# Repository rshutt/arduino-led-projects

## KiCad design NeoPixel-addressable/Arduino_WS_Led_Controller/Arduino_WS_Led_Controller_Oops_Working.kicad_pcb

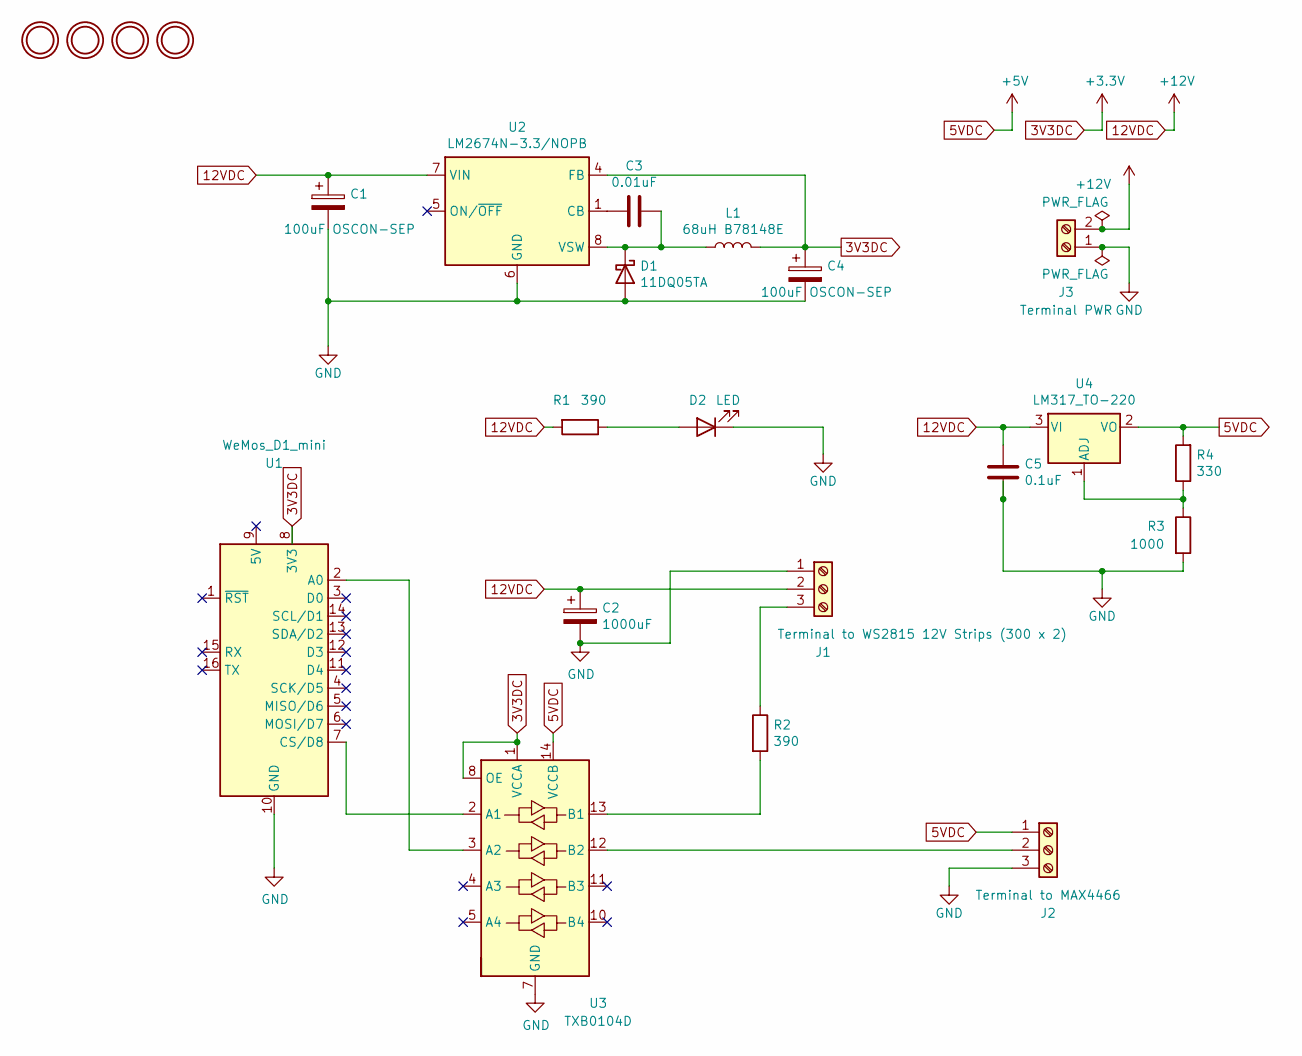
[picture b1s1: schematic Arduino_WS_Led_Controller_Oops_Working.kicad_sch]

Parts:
C1, C4: 100uF OSCON-SEP; CP_Radial_D8.0mm_P3.50mm
C2: 1000uF; CP_Radial_D10.0mm_P2.50mm
C3: 0.01uF; C_Disc_D5.0mm_W2.5mm_P5.00mm
C5: 0.1uF; C_Disc_D5.0mm_W2.5mm_P5.00mm
D1: 11DQ05TA; D_A-405_P7.62mm_Horizontal
D2: LED; LED_D5.0mm_Clear
J1: Terminal to WS2815 12V Strips (300 x 2); TerminalBlock_Altech_AK300-3_P5.00mm
J2: Terminal to MAX4466; TerminalBlock_Altech_AK300-3_P5.00mm
J3: Terminal PWR; TerminalBlock_Altech_AK300-2_P5.00mm
L1: 68uH B78148E; L_Axial_L14.0mm_D4.5mm_P5.08mm_Vertical_Fastron_LACC
R1, R2: 390; R_Axial_DIN0207_L6.3mm_D2.5mm_P7.62mm_Horizontal
R3: 1000; R_Axial_DIN0207_L6.3mm_D2.5mm_P7.62mm_Horizontal
R4: 330; R_Axial_DIN0207_L6.3mm_D2.5mm_P7.62mm_Horizontal
U1: WeMos_D1_mini; WEMOS_D1_mini_light
U2: LM2674N-3.3/NOPB; DIP-8_W7.62mm_Socket
U3: TXB0104D; SOIC-14_3.9x8.7mm_P1.27mm
U4: LM317_TO-220; TO-220-3_Vertical
U5, U6, U7, U8: MOUNTINGHOLE3.0THIN; MountingHole_3.2mm_M3

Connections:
3V3DC: C4.1, L1.2, U1.8 (3V3), U2.4 (FB), U3.1 (VCCA), U3.8 (OE)
5VDC: J2.1, R4.2, U3.14 (VCCB), U4.2 (VO)
12VDC: C1.1, C2.1, C5.1, J1.2, J3.2, R1.2, U2.7 (VIN), U4.3 (VI)
GND: C1.2, C2.2, C4.2, C5.2, D1.2 (A), D2.1 (K), J1.1, J2.3, J3.1, R3.2, U1.10 (GND), U2.6 (GND), U3.7 (GND)
unnamed: C3.1, D1.1 (K), L1.1, U2.8 (VSW)
unnamed: C3.2, U2.1 (CB)
unnamed: D2.2 (A), R1.1
unnamed: J1.3, R2.1
unnamed: J2.2, U3.12 (B2)
unnamed: R2.2, U3.13 (B1)
unnamed: R3.1, R4.1, U4.1 (ADJ)
unnamed: U1.2 (A0), U3.3 (A2)
unnamed: U1.7 (CS/D8), U3.2 (A1)

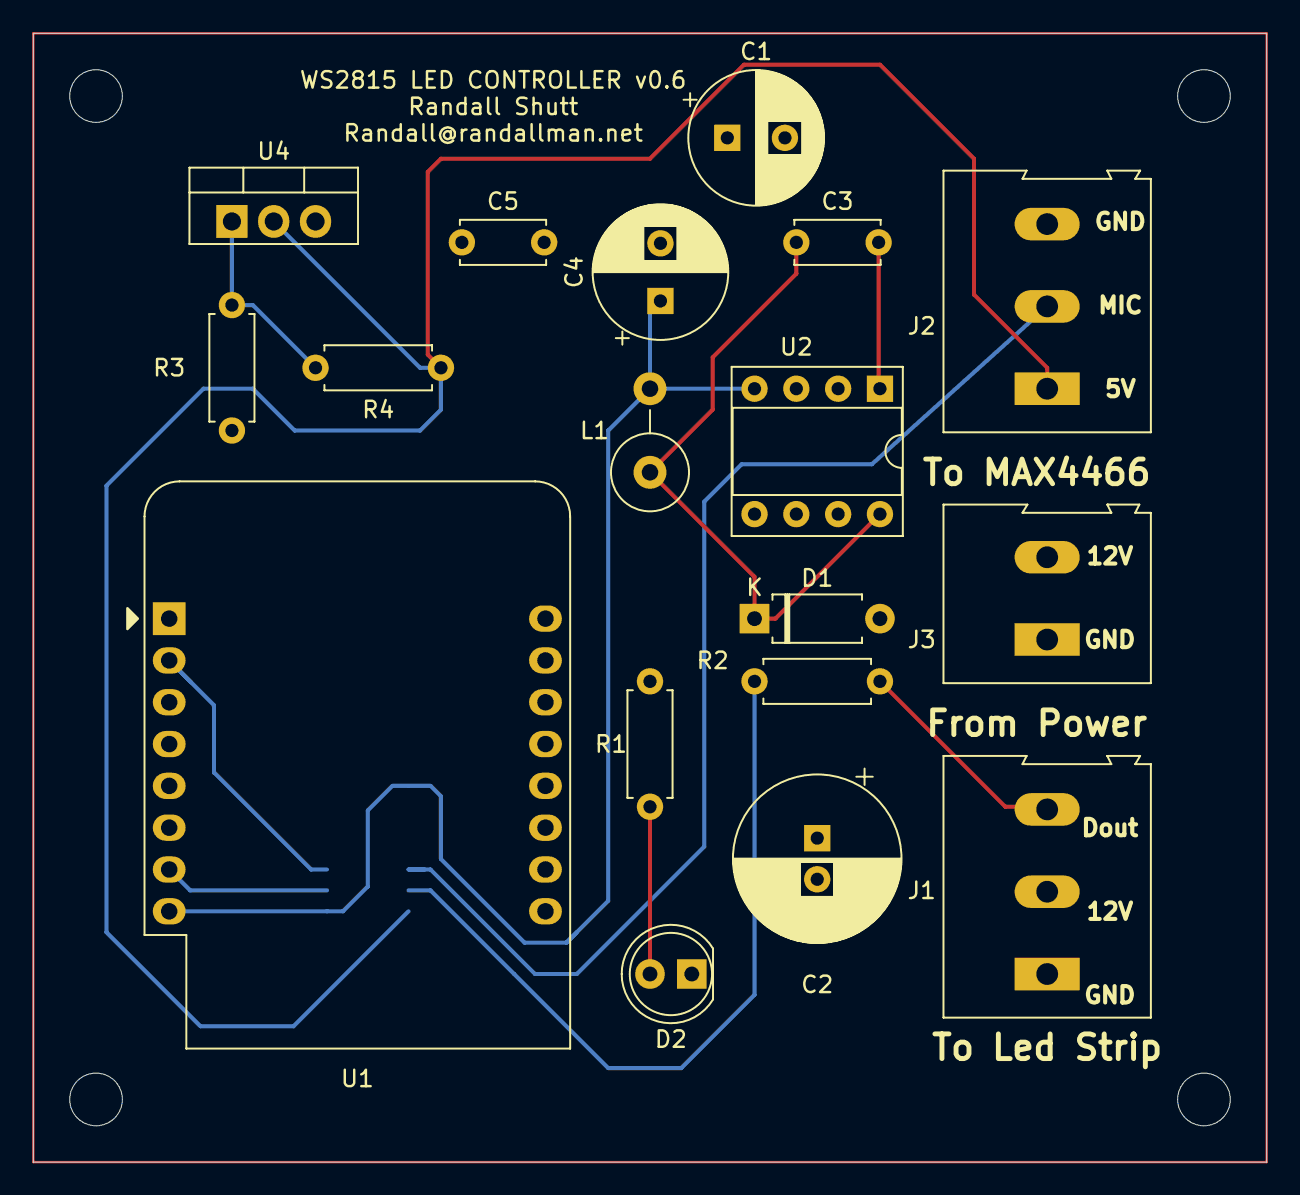
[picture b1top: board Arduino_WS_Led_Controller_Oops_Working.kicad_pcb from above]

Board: 2 copper layers, 74.9 x 68.6 mm, 23 parts (1 on the bottom side), 13 nets.

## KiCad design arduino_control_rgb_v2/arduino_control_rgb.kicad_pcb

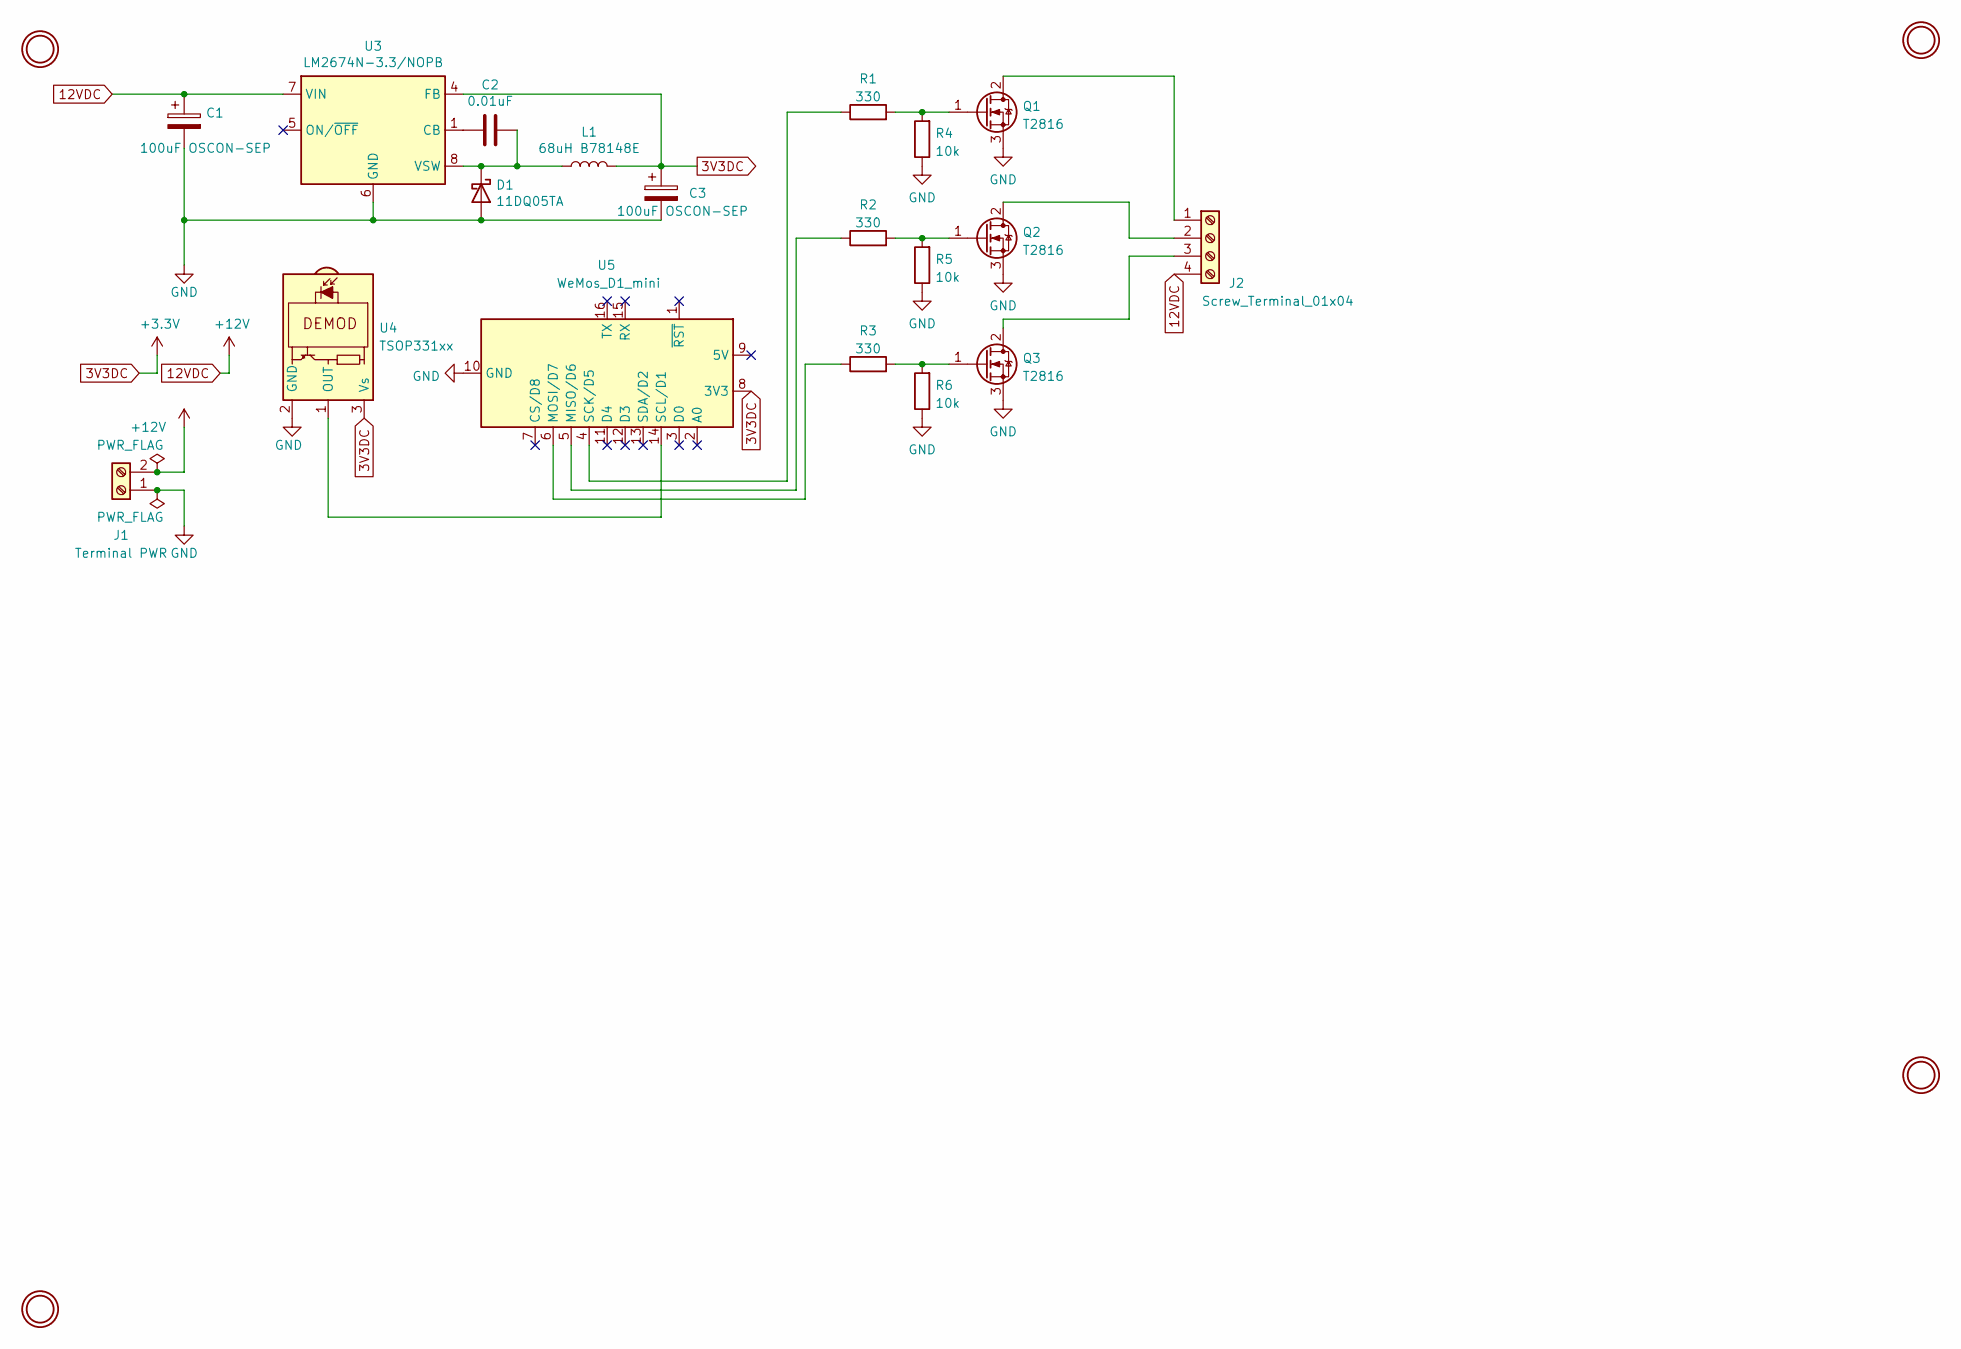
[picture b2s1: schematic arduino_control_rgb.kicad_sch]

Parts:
C1, C3: 100uF OSCON-SEP; CP_Radial_D8.0mm_P3.50mm
C2: 0.01uF; C_Disc_D5.0mm_W2.5mm_P5.00mm
D1: 11DQ05TA; D_A-405_P7.62mm_Horizontal
J1: Terminal PWR; TerminalBlock_4Ucon_1x02_P3.50mm_Horizontal
J2: Screw_Terminal_01x04; TerminalBlock_4Ucon_1x04_P3.50mm_Horizontal
L1: 68uH B78148E; L_Axial_L14.0mm_D4.5mm_P5.08mm_Vertical_Fastron_LACC
Q1, Q2, Q3: T2816; TO-220-3_Vertical
R1, R2, R3: 330; R_Axial_DIN0204_L3.6mm_D1.6mm_P7.62mm_Horizontal
R4, R5, R6: 10k; R_Axial_DIN0204_L3.6mm_D1.6mm_P7.62mm_Horizontal
U1, U2, U6, U7: MOUNTINGHOLE3.0THIN; MountingHole_3.2mm_M3
U3: LM2674N-3.3/NOPB; DIP-8_W7.62mm_Socket
U4: TSOP331xx; Vishay_MINIMOLD-3Pin
U5: WeMos_D1_mini; WEMOS_D1_mini_light

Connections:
3V3DC: C3.1, L1.2, U3.4 (FB), U4.3 (Vs), U5.8 (3V3)
12VDC: C1.1, J1.2, J2.4, U3.7 (VIN)
GND: C1.2, C3.2, D1.2 (A), J1.1, Q1.3 (S), Q2.3 (S), Q3.3 (S), R4.1, R5.1, R6.1, U3.6 (GND), U4.2 (GND), U5.10 (GND)
unnamed: C2.1, D1.1 (K), L1.1, U3.8 (VSW)
unnamed: C2.2, U3.1 (CB)
unnamed: J2.1, Q1.2 (D)
unnamed: J2.2, Q2.2 (D)
unnamed: J2.3, Q3.2 (D)
unnamed: Q1.1 (G), R1.2, R4.2
unnamed: Q2.1 (G), R2.2, R5.2
unnamed: Q3.1 (G), R3.2, R6.2
unnamed: R1.1, U5.4 (SCK/D5)
unnamed: R2.1, U5.5 (MISO/D6)
unnamed: R3.1, U5.6 (MOSI/D7)
unnamed: U4.1 (OUT), U5.14 (SCL/D1)

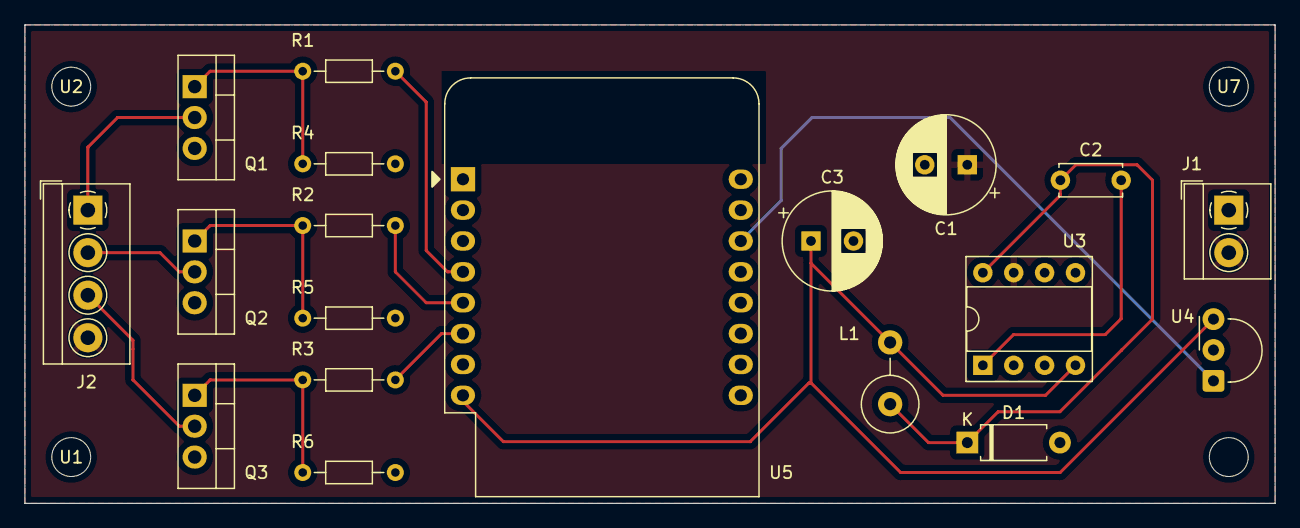
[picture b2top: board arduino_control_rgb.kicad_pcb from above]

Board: 2 copper layers, 102.9 x 39.4 mm, 23 parts (0 on the bottom side), 15 nets.

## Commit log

2021-09-25 Adding 5050_strand.ino
2021-09-25 Adding debug
2021-09-25 Moved
2021-09-25 Anew apparoch
2021-09-26 This is the addressable project
2021-10-12 Adding the PCB and Schematic
2021-10-18 Getting the PCB set
2021-10-18 move trace from R4
2021-10-18 Final 0.5
2021-12-20 Made WM_Configer into a library-ish... still need to version etc...
2021-12-20 Added README.md for WM_Configer
2021-12-20 ```s in wrong place
2021-12-20 Added more howto
2022-04-09 Interim commit
